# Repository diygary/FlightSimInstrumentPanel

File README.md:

Please visit https://www.diygary.com/instrumentpanel for more info.

NOTE: Not all dials/switches on the PCB are functional due to limitations with the SimConnect display (lack of writeable Simulation Variables)

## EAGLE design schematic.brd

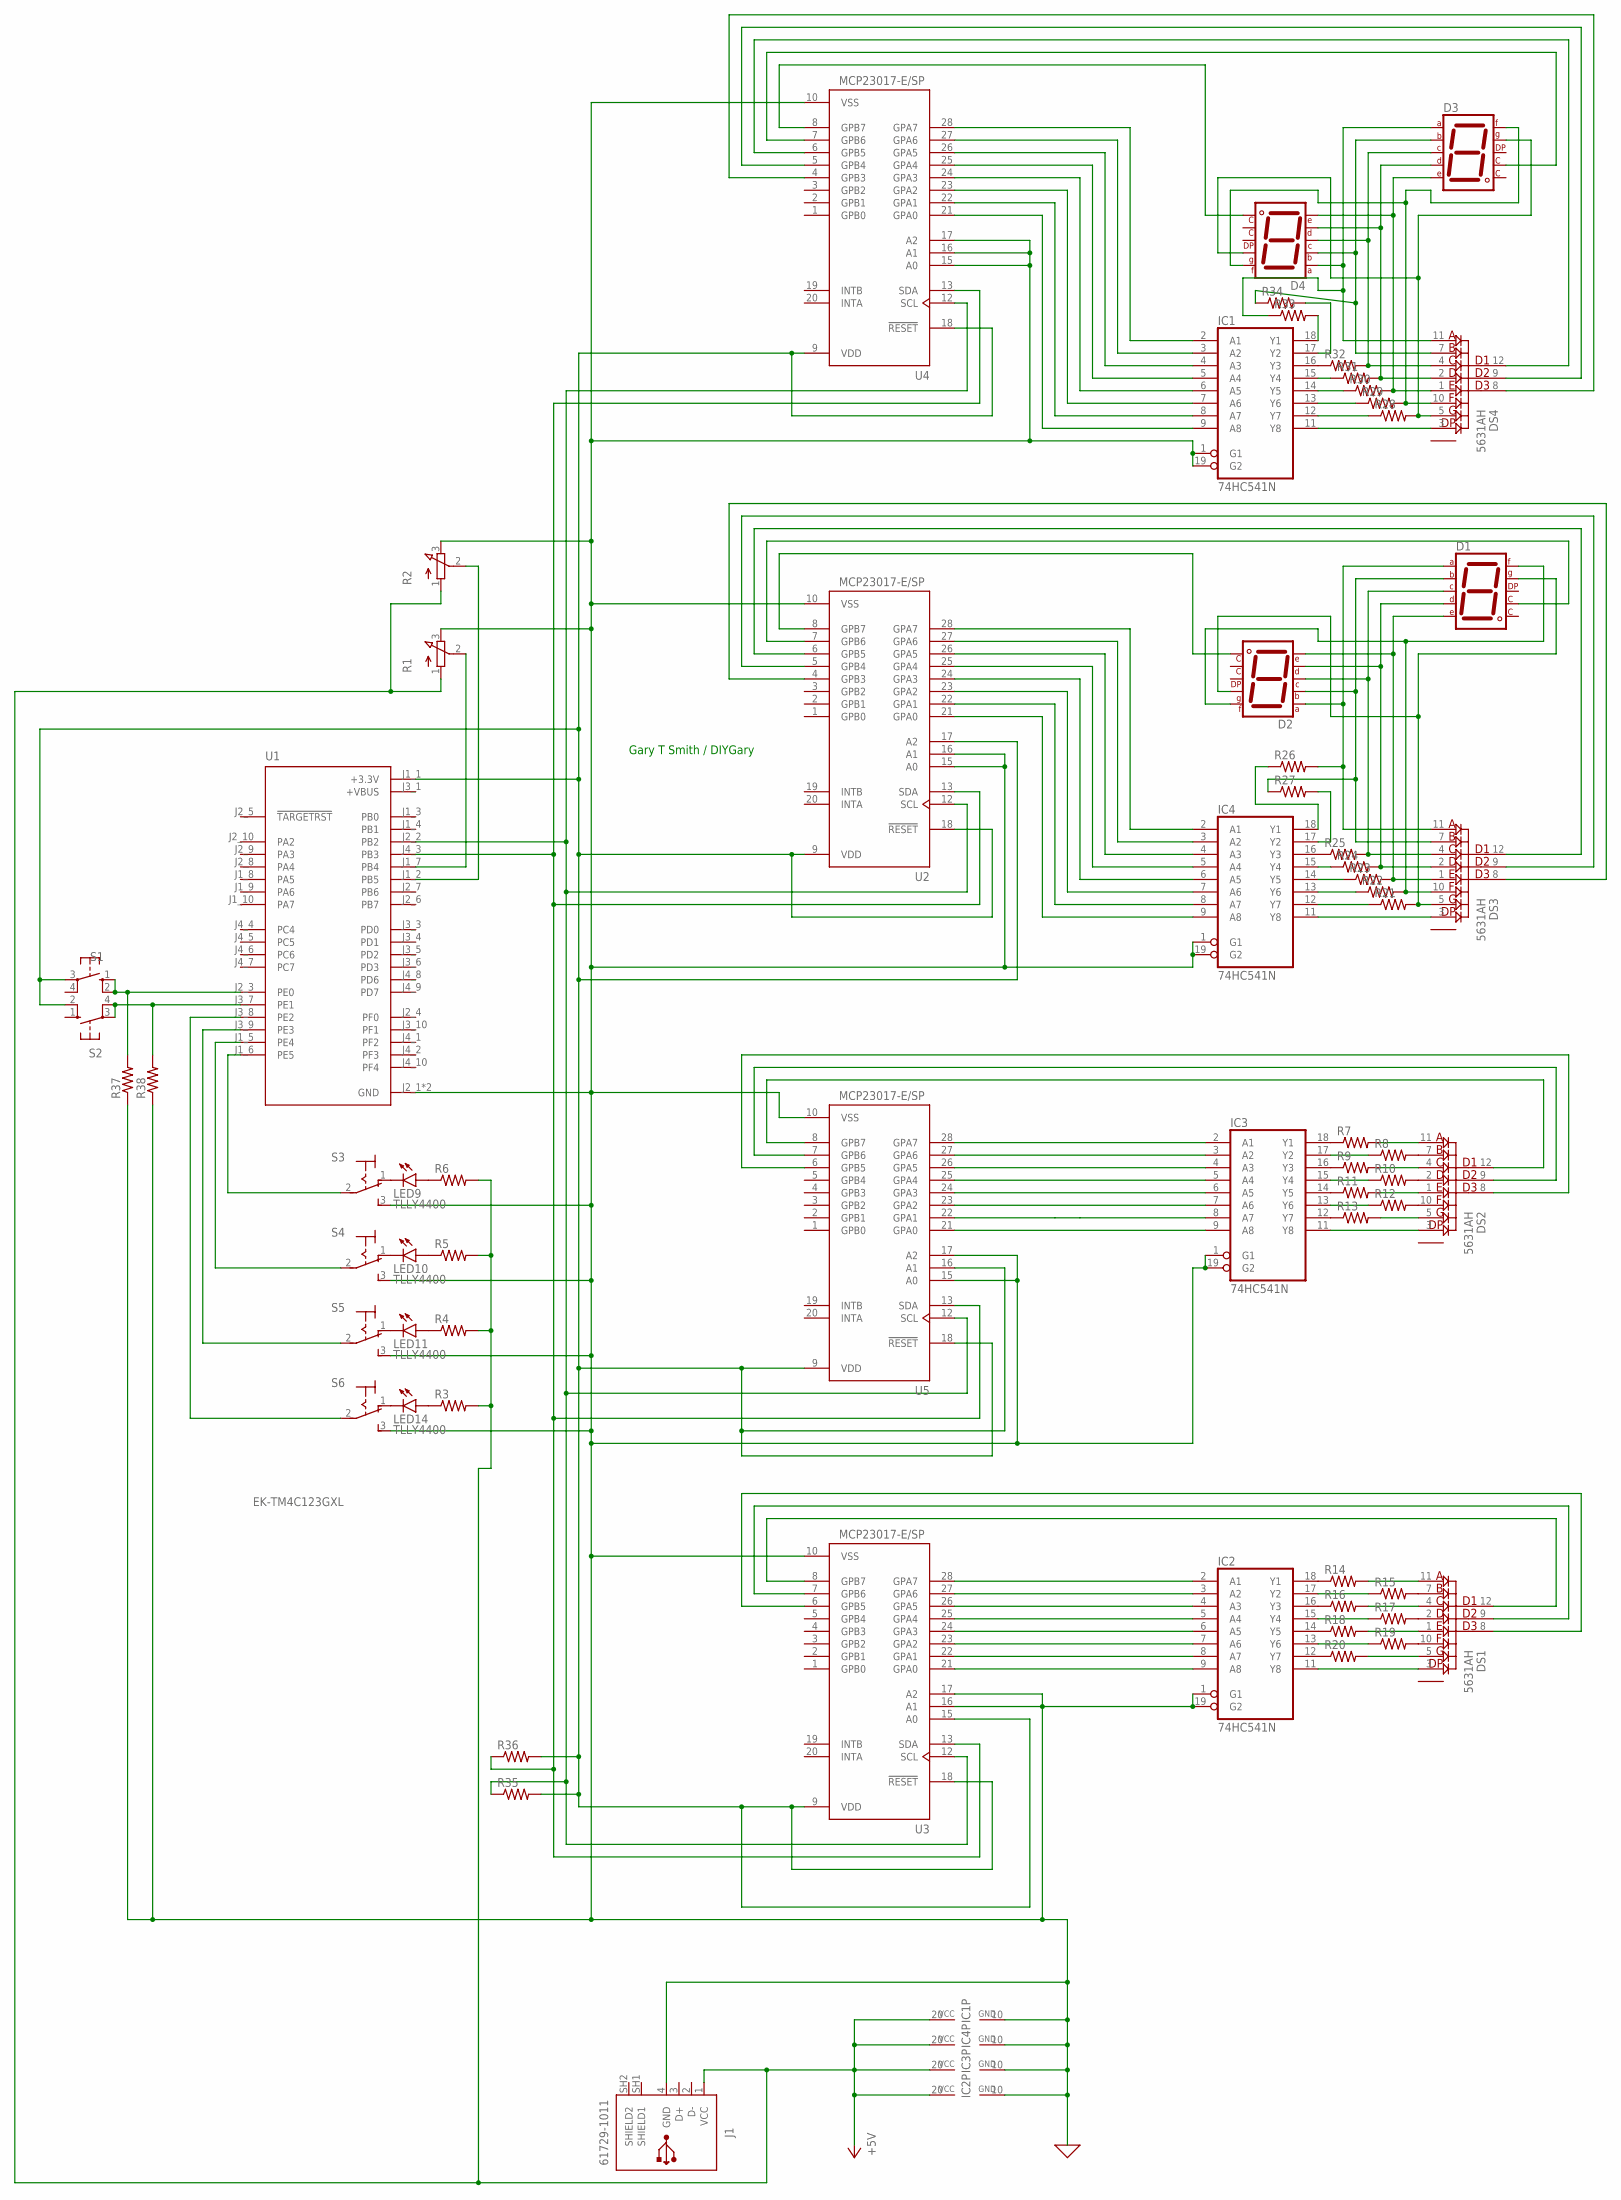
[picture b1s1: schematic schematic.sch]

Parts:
D1, D2, D3, D4: 5611AH
DS1, DS2, DS3, DS4: 5631AH; DIPS1524W50P254L3760H835Q12N
IC1, IC2, IC3, IC4: 74HC541N; DIL20
J1: 61729-1011; 61729-1011BLF
LED9, LED10, LED11, LED14: TLLY4400; LED3MM
R1, R2: 3RP/1610N
R3, R4, R5, R6, R7, R8, R9, R10, R11, R12, R13, R14, R15, R16, R17, R18, R19, R20, R21, R22, R23, R24, R25, R26, R27, R28, R29, R30, R31, R32, R33, R34, R35, R36, R37, R38: R-US_0204/7; 0204/7
S1, S2: 10-XX; B3F-10XX
S3, S4, S5, S6: 320-916
U1: EK-TM4C123GXL; MODULE_EK-TM4C123GXL
U2, U3, U4, U5: MCP23017-E/SP; DIP787W45P254L3556H508Q28

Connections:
0: IC1.1 (G1), IC1.10 (GND), IC1.19 (G2), IC2.1 (G1), IC2.10 (GND), IC2.19 (G2), IC3.1 (G1), IC3.10 (GND), IC3.19 (G2), IC4.1 (G1), IC4.10 (GND), IC4.19 (G2), J1.4 (GND), R1.3 (E), R2.3 (E), R37.1, R38.1, S3.3 (S), S4.3 (S), S5.3 (S), S6.3 (S), U1.J2_1 (GND), U1.J3_2 (GND), U2.10 (VSS), U2.15 (A0), U2.16 (A1), U3.10 (VSS), U3.16 (A1), U3.17 (A2), U4.10 (VSS), U4.15 (A0), U4.16 (A1), U4.17 (A2), U5.10 (VSS), U5.15 (A0), U5.17 (A2)
+VBUS: U1.J3_1 (+VBUS)
unnamed: IC1.9 (A8), U4.21 (GPA0)
unnamed: DS1.7 (A_B), R15.2
unnamed: DS1.2 (A_D), R17.2
unnamed: DS1.10 (A_F), R19.2
unnamed: DS2.7 (A_B), R8.2
unnamed: DS2.2 (A_D), R10.2
unnamed: DS2.10 (A_F), R12.2
unnamed: D3.7 (A), D4.7 (A), DS4.11 (A_A), R33.1
unnamed: IC1.8 (A7), U4.22 (GPA1)
unnamed: IC1.7 (A6), U4.23 (GPA2)
unnamed: IC1.6 (A5), U4.24 (GPA3)
unnamed: IC1.5 (A4), U4.25 (GPA4)
unnamed: IC1.4 (A3), U4.26 (GPA5)
unnamed: IC1.3 (A2), U4.27 (GPA6)
unnamed: IC1.2 (A1), U4.28 (GPA7)
unnamed: D3.3 (CK1), U4.7 (GPB6)
unnamed: DS4.12 (CC_D1), U4.6 (GPB5)
unnamed: DS4.9 (CC_D2), U4.5 (GPB4)
unnamed: DS4.8 (CC_D3), U4.4 (GPB3)
unnamed: D1.7 (A), D2.7 (A), DS3.11 (A_A), R26.2
unnamed: IC1.16 (Y3), R32.1
unnamed: IC1.12 (Y7), R28.1
unnamed: IC1.13 (Y6), R29.1
unnamed: D1.1 (E), D2.1 (E), DS3.1 (A_E), R23.2
unnamed: IC1.14 (Y5), R30.1
unnamed: IC1.15 (Y4), R31.1
unnamed: DS3.3 (A_DP), IC4.11 (Y8)
unnamed: DS4.3 (A_DP), IC1.11 (Y8)
unnamed: DS3.9 (CC_D2), U2.5 (GPB4)
unnamed: D1.3 (CK1), U2.7 (GPB6)
unnamed: DS3.12 (CC_D1), U2.6 (GPB5)
unnamed: DS3.8 (CC_D3), U2.4 (GPB3)
unnamed: IC4.9 (A8), U2.21 (GPA0)
unnamed: IC4.8 (A7), U2.22 (GPA1)
unnamed: IC4.7 (A6), U2.23 (GPA2)
unnamed: IC4.6 (A5), U2.24 (GPA3)
unnamed: IC4.5 (A4), U2.25 (GPA4)
unnamed: IC4.4 (A3), U2.26 (GPA5)
unnamed: IC4.3 (A2), U2.27 (GPA6)
unnamed: IC4.2 (A1), U2.28 (GPA7)
unnamed: IC3.18 (Y1), R7.1
unnamed: IC1.20 (VCC), IC2.20 (VCC), IC3.20 (VCC), IC4.20 (VCC), J1.1 (VCC), R1.1 (A), R2.1 (A), R3.2, R4.2, R5.2, R6.2
unnamed: IC3.16 (Y3), R9.1
unnamed: IC3.14 (Y5), R11.1
unnamed: IC3.12 (Y7), R13.1
unnamed: DS2.3 (A_DP), IC3.11 (Y8)
unnamed: DS2.12 (CC_D1), U5.8 (GPB7)
unnamed: DS2.9 (CC_D2), U5.7 (GPB6)
unnamed: DS2.8 (CC_D3), U5.6 (GPB5)
unnamed: IC3.2 (A1), U5.28 (GPA7)
unnamed: IC3.3 (A2), U5.27 (GPA6)
unnamed: IC3.4 (A3), U5.26 (GPA5)
unnamed: IC3.5 (A4), U5.25 (GPA4)
unnamed: IC3.6 (A5), U5.24 (GPA3)
unnamed: IC3.7 (A6), U5.23 (GPA2)
unnamed: IC3.8 (A7), U5.22 (GPA1)
unnamed: IC3.9 (A8), U5.21 (GPA0)
unnamed: IC2.2 (A1), U3.28 (GPA7)
unnamed: IC2.3 (A2), U3.27 (GPA6)
unnamed: IC2.4 (A3), U3.26 (GPA5)
unnamed: IC2.5 (A4), U3.25 (GPA4)
unnamed: IC2.6 (A5), U3.24 (GPA3)
unnamed: IC2.7 (A6), U3.23 (GPA2)
unnamed: IC2.8 (A7), U3.22 (GPA1)
unnamed: IC2.9 (A8), U3.21 (GPA0)
unnamed: IC2.18 (Y1), R14.1
unnamed: IC2.16 (Y3), R16.1
unnamed: IC2.14 (Y5), R18.1
unnamed: IC2.12 (Y7), R20.1
unnamed: DS1.3 (A_DP), IC2.11 (Y8)
unnamed: DS1.12 (CC_D1), U3.8 (GPB7)
unnamed: DS1.9 (CC_D2), U3.7 (GPB6)
unnamed: DS1.8 (CC_D3), U3.6 (GPB5)
unnamed: LED14.K (C), S6.1 (O)
unnamed: D2.8 (CK2), U2.8 (GPB7)
unnamed: DS1.5 (A_G), R20.2
unnamed: D4.8 (CK2), U4.8 (GPB7)
unnamed: LED10.K (C), S4.1 (O)
unnamed: S3.2, U1.J1_6 (PE5)
unnamed: S4.2, U1.J1_5 (PE4)
unnamed: S5.2, U1.J3_9 (PE3)
unnamed: S6.2, U1.J3_8 (PE2)
unnamed: LED14.A, R3.1
unnamed: LED11.K (C), S5.1 (O)
unnamed: LED11.A, R4.1
unnamed: LED9.K (C), S3.1 (O)
unnamed: LED10.A, R5.1
unnamed: LED9.A, R6.1
unnamed: R38.2, S2.3, S2.4 (P1), U1.J3_7 (PE1)
unnamed: R37.2, S1.1 (S), S1.2 (S1), U1.J2_3 (PE0)
unnamed: R1.2 (S), U1.J1_7 (PB4)
unnamed: R2.2 (S), U1.J1_2 (PB5)
unnamed: R35.1, U1.J2_2 (PB2), U2.12 (SCL), U3.12 (SCL), U4.12 (SCL), U5.12 (SCL)
unnamed: R36.1, U1.J4_3 (PB3), U2.13 (SDA), U3.13 (SDA), U4.13 (SDA), U5.13 (SDA)
unnamed: R35.2, R36.2, S1.3, S2.2 (S1), U1.J1_1 (+3.3V), U2.9 (VDD), U2.17 (A2), U2.18 (!RESET), U3.9 (VDD), U3.15 (A0), U3.18 (!RESET), U4.9 (VDD), U4.18 (!RESET), U5.9 (VDD), U5.16 (A1), U5.18 (!RESET)
unnamed: IC2.13 (Y6), R19.1
unnamed: DS1.1 (A_E), R18.2
unnamed: IC2.15 (Y4), R17.1
unnamed: DS1.4 (A_C), R16.2
unnamed: IC2.17 (Y2), R15.1
unnamed: DS1.11 (A_A), R14.2
unnamed: DS2.5 (A_G), R13.2
unnamed: IC3.13 (Y6), R12.1
unnamed: DS2.1 (A_E), R11.2
unnamed: IC3.15 (Y4), R10.1
unnamed: DS2.4 (A_C), R9.2
unnamed: IC3.17 (Y2), R8.1
unnamed: DS2.11 (A_A), R7.2
unnamed: IC1.18 (Y1), R33.2
unnamed: D1.6 (B), D2.6 (B), DS3.7 (A_B), R27.1
unnamed: D1.4 (C), D2.4 (C), DS3.4 (A_C), R25.2
unnamed: D1.2 (D), D2.2 (D), DS3.2 (A_D), R24.2
unnamed: D1.9 (F), D2.9 (F), DS3.10 (A_F), R22.2
unnamed: D1.10 (G), D2.10 (G), DS3.5 (A_G), R21.2
unnamed: IC1.17 (Y2), R34.2
unnamed: D3.6 (B), D4.6 (B), DS4.7 (A_B), R34.1
unnamed: D3.4 (C), D4.4 (C), DS4.4 (A_C), R32.2
unnamed: D3.2 (D), D4.2 (D), DS4.2 (A_D), R31.2
unnamed: D3.1 (E), D4.1 (E), DS4.1 (A_E), R30.2
unnamed: D3.9 (F), D4.9 (F), DS4.10 (A_F), R29.2
unnamed: D3.10 (G), D4.10 (G), DS4.5 (A_G), R28.2
unnamed: IC4.16 (Y3), R25.1
unnamed: IC4.15 (Y4), R24.1
unnamed: IC4.14 (Y5), R23.1
unnamed: IC4.13 (Y6), R22.1
unnamed: IC4.12 (Y7), R21.1
unnamed: IC4.18 (Y1), R26.1
unnamed: IC4.17 (Y2), R27.2

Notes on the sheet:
Gary T Smith / DIYGary

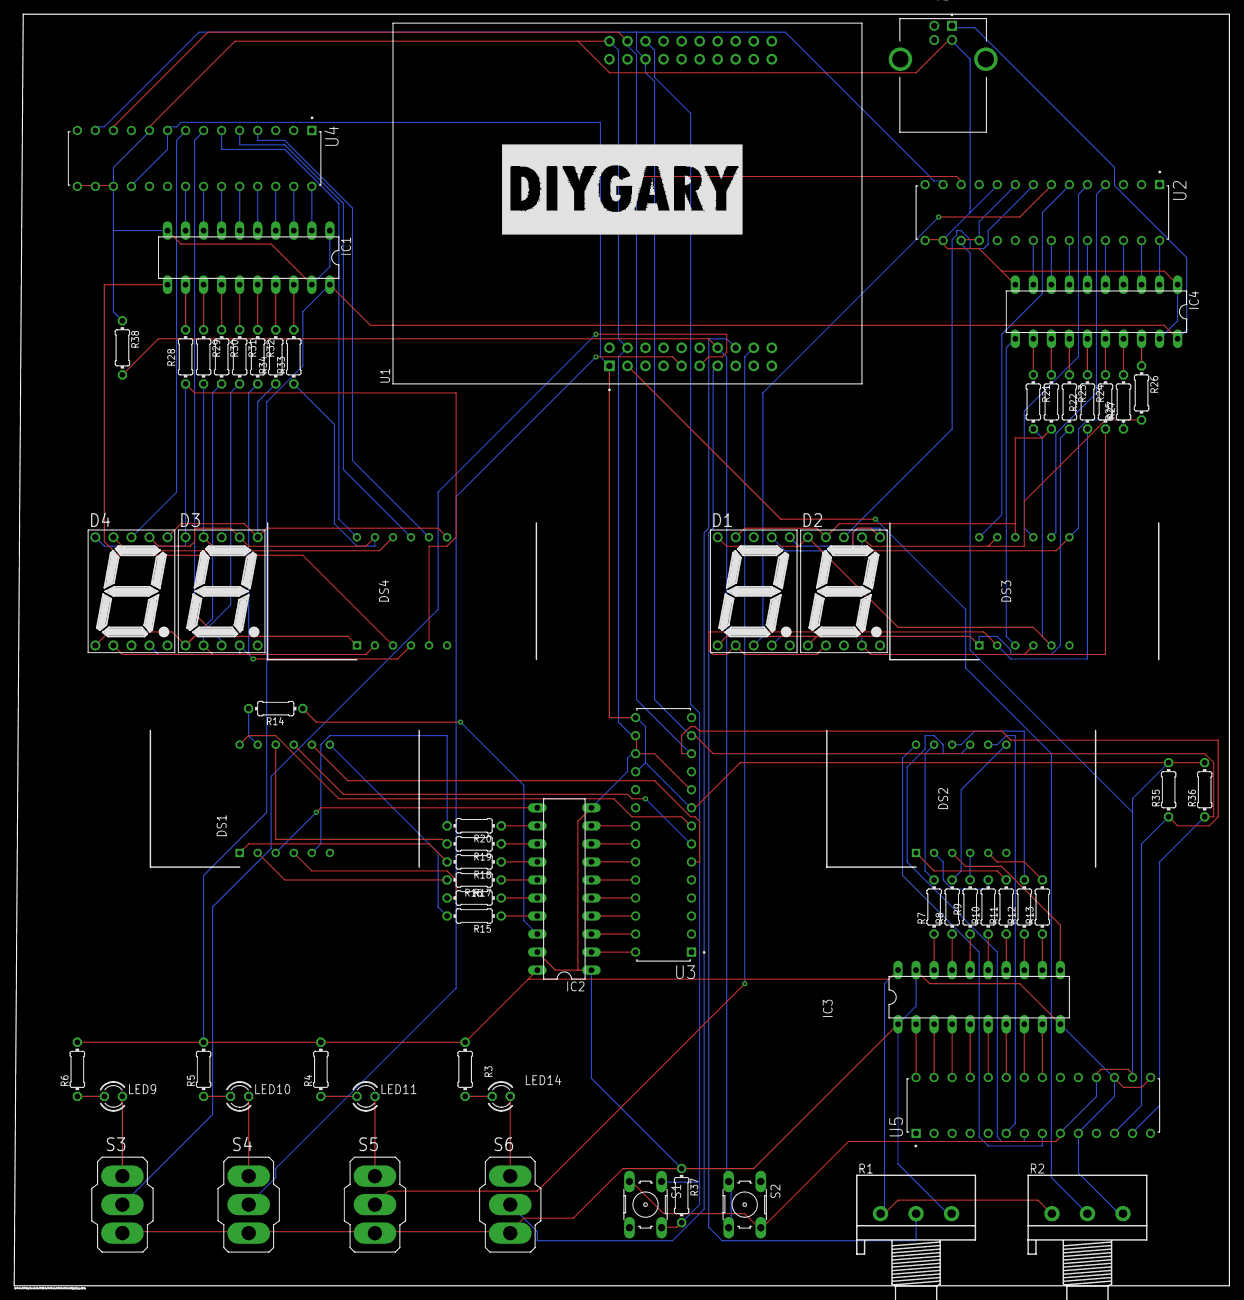
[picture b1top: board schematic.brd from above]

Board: 2 copper layers, 171.1 x 179.1 mm, 66 parts (0 on the bottom side), 129 nets.

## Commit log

2021-06-18 Schematic finished, board partially done
2021-06-20 Final version
2021-06-28 Port initializations finished, I2C init finished
2021-07-31 half done, working on pc-to-mcu comm
2021-07-31 pc-to-MCU communication works
2021-08-01 official schematic of board
2021-08-02 gets msfs data and sends to MCU
2021-08-02 Telemetry Data fully functional
2021-08-02 schematics and board files not available
2021-08-05 done for now
    Flight data display fully functional, inputs are partially functional --- still fidgety, and are limited by the amount of simulation variables that are set to Read-Only in MSFS
2021-08-06 notes
